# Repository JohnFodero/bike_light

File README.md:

# bike_light
A lithium powered, uC controlled bike light. For safety!

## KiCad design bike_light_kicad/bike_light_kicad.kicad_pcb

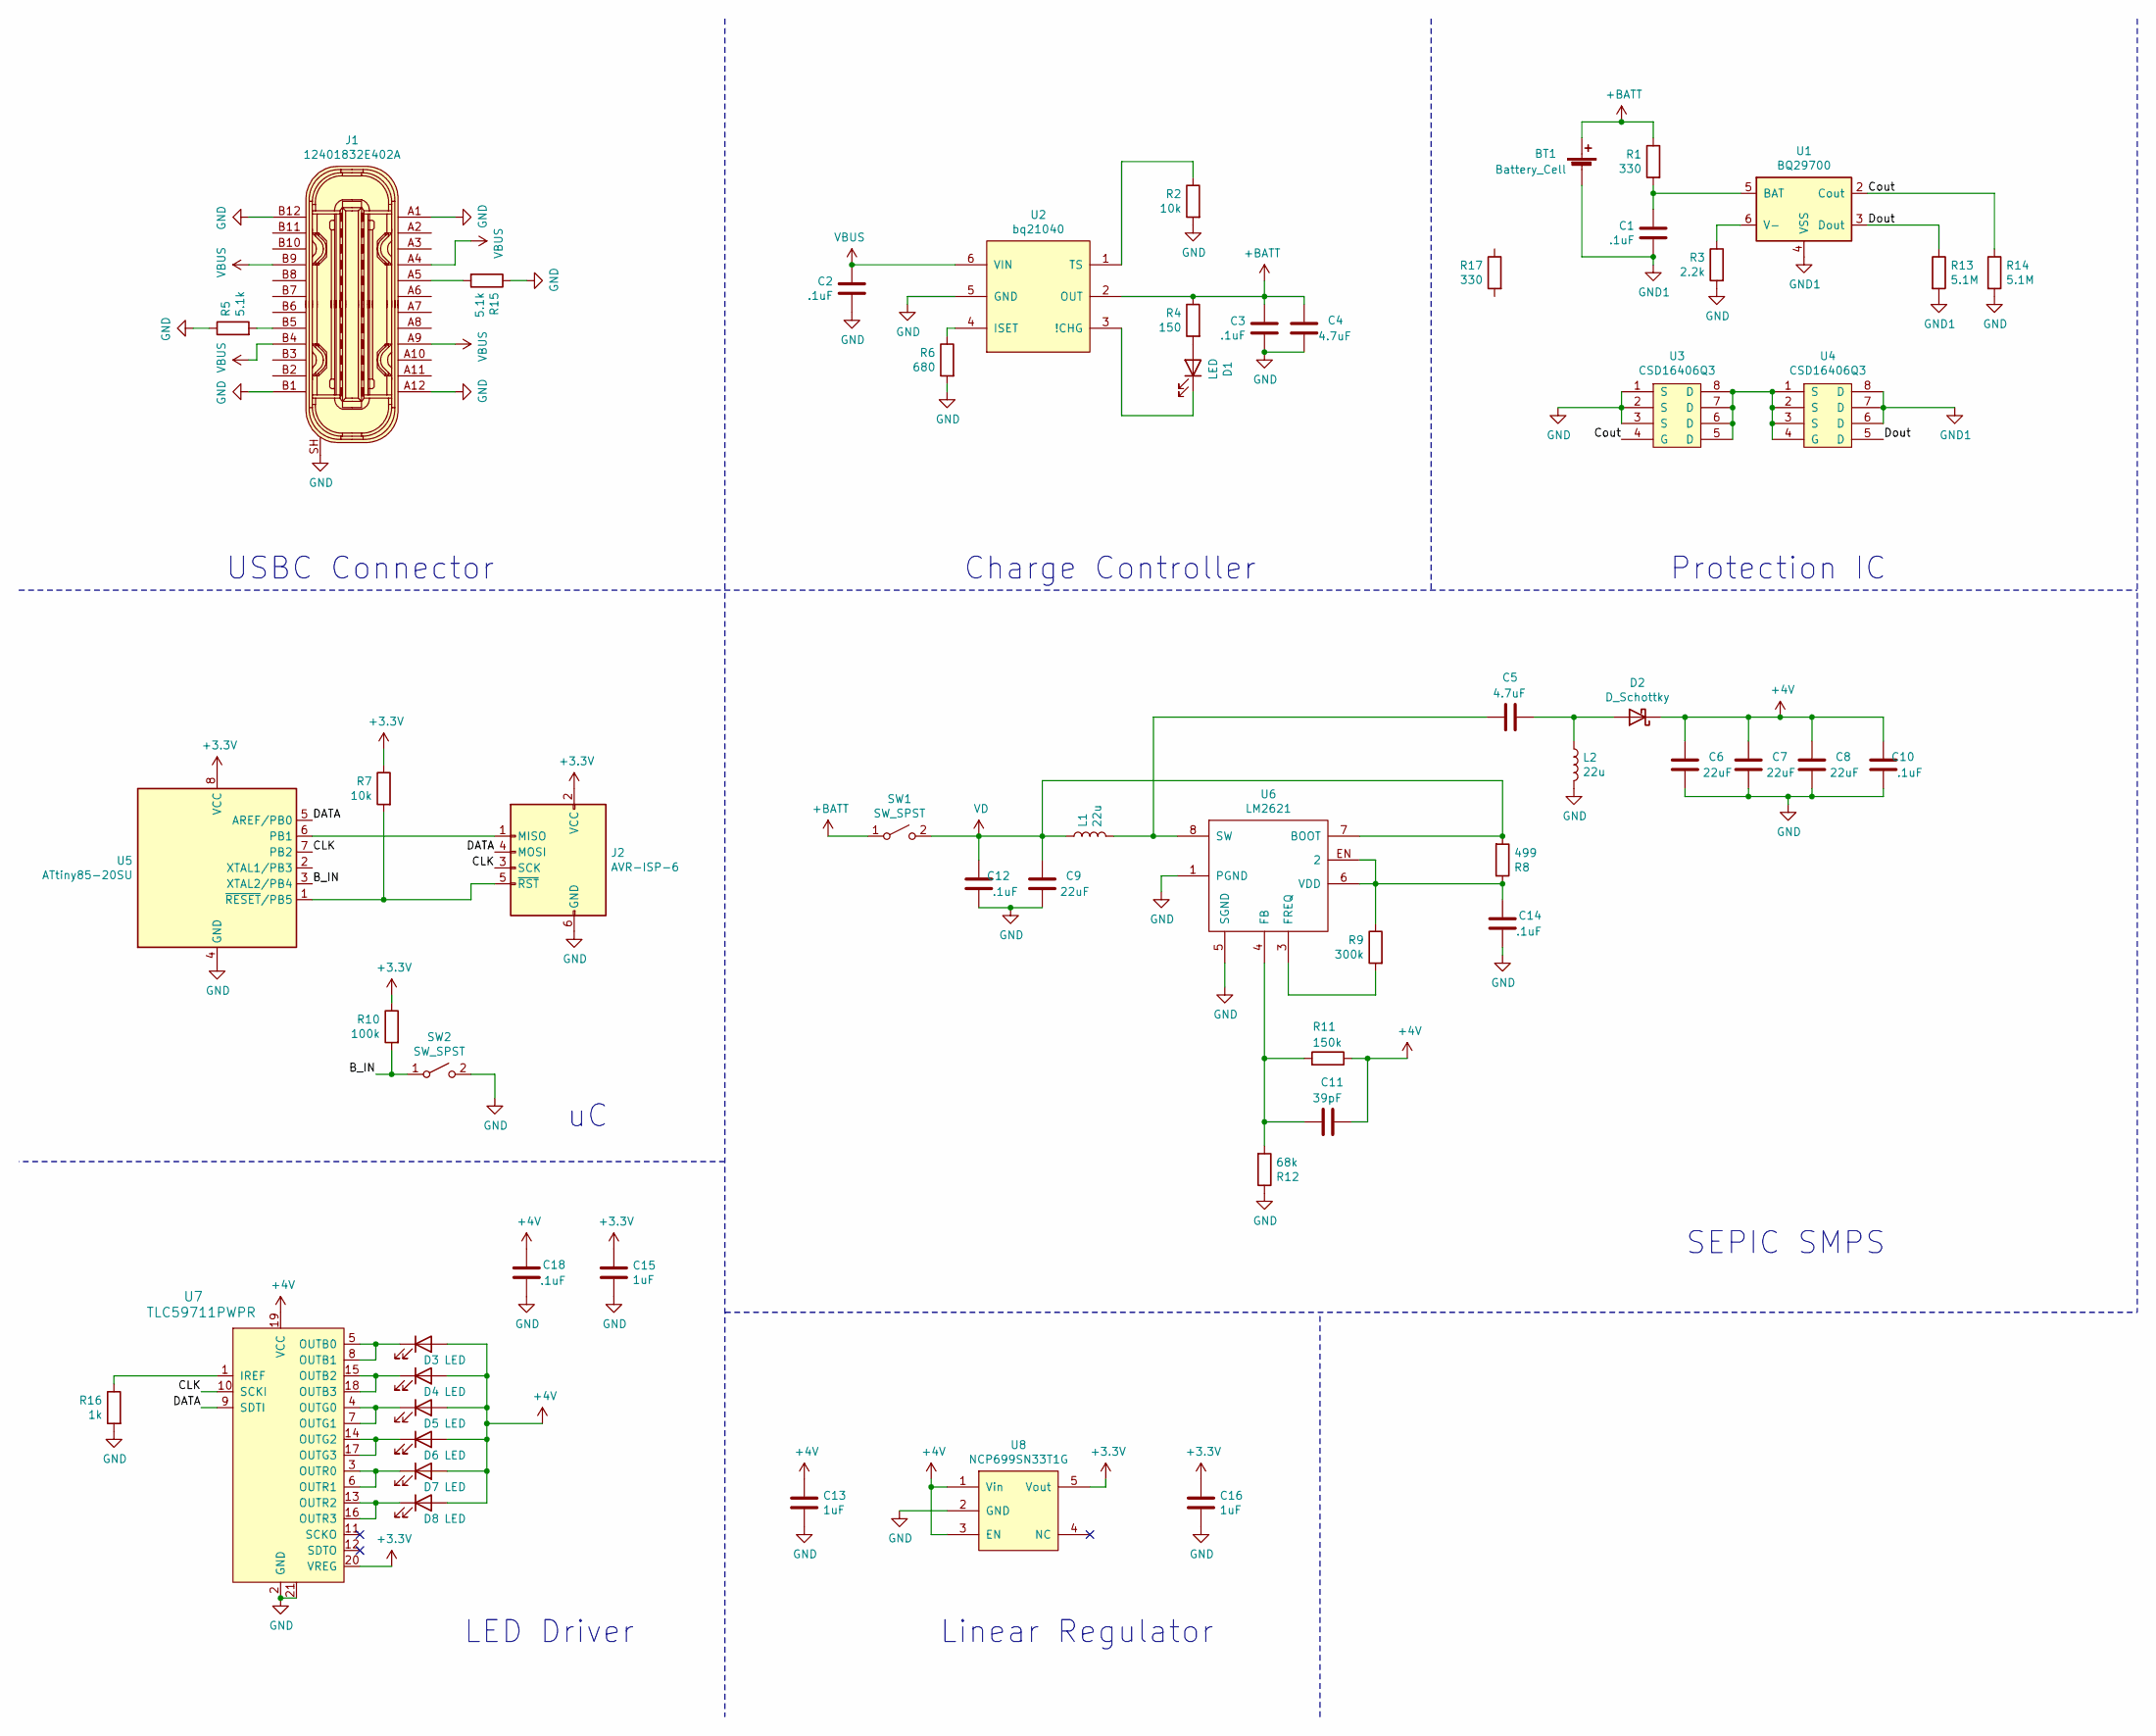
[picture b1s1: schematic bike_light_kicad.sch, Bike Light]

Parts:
BT1: Battery_Cell; 36-254-ND; MPN PRT-12895; Digi-Key_PN 1568-1488-ND
C1, C2, C3, C10, C12, C14, C18: .1uF; C_0603; MPN C0603C104M4RACTU; Digi-Key_PN 399-1099-1-ND
C4: 4.7uF; C_0603; MPN CL10A475MO8NNNC; Digi-Key_PN 1276-1904-1-ND
C5: 4.7uF; C_1206; MPN C1206C475K4RACTU; Digi-Key_PN 399-3524-1-ND
C6, C7, C8, C9: 22uF; C_0805; MPN GRM21BC81C226ME44L; Digi-Key_PN 490-9956-1-ND
C11: 39pF; C_0603; MPN C0603C390J5GACTU; Digi-Key_PN 399-7911-1-ND
C13, C15, C16: 1uF; C_0603; MPN C0603C105M4RACTU; Digi-Key_PN 399-11136-1-ND
D1: LED; LED_0603; MPN LTST-C190KFKT; Digi-Key_PN 160-1434-1-ND
D2: D_Schottky; D_SOD-323F; MPN PMEG2015EJ,115; Digi-Key_PN 1727-3861-2-ND
D3, D4, D5, D6, D7, D8: LED; 1510-2183-1-ND; MPN SPMWHT541ML5XATMS6; Digi-Key_PN 1510-2183-1-ND
J1: 12401832E402A; USB_Type_C_Female__12401610E4_2A; MPN 12401832E402A; Digi-Key_PN 12401832E402ACT-ND
J2: AVR-ISP-6; PINHEAD1-6; MPN 4173; Digi-Key_PN 1528-2946-ND
L1, L2: 22u; SRU1038-220YCT-ND; MPN SRU1038-220Y; Digi-Key_PN SRU1038-220YCT-ND
R1, R17: 330; R_0603; MPN RC0603FR-07330RL; Digi-Key_PN 311-330HRCT-ND
R2, R7: 10k; R_0603; MPN RC0603FR-0710KL; Digi-Key_PN 311-10.0KHRCT-ND
R3: 2.2k; R_0603; MPN RC0603FR-072K2L; Digi-Key_PN 311-2.20KHRCT-ND
R4: 150; R_0603; MPN RC0603FR-07150RL; Digi-Key_PN 311-150HRCT-ND
R5, R15: 5.1k; R_0603; MPN RC0603FR-075K1L; Digi-Key_PN 311-5.10KHRCT-ND
R6: 680; R_0603; MPN RT0603FRE07680RL; Digi-Key_PN YAG3356CT-ND
R8: 499; R_0603; MPN RC0603FR-07499RL; Digi-Key_PN 311-499HRCT-ND
R9: 300k; R_0603; MPN RC0603FR-07300KL; Digi-Key_PN 311-300KHRCT-ND
R10: 100k; R_0603; MPN RC0603FR-07100KL; Digi-Key_PN 311-100KHRCT-ND
R11: 150k; R_0603; MPN RC0603FR-07150KL; Digi-Key_PN 311-150KHRCT-ND
R12: 68k; R_0603; MPN RC0603FR-0768KL; Digi-Key_PN 311-68.0KHRCT-ND
R13, R14: 5.1M; R_0603; MPN RC0603JR-075M1L; Digi-Key_PN 311-5.1MGRCT-ND
R16: 1k; R_0603; MPN RC0603FR-071KL; Digi-Key_PN 311-1.00KHRCT-ND
SW1: SW_SPST; CKC5106-ND; MPN L101011MS02Q; Digi-Key_PN CKC5106-ND
SW2: SW_SPST
U1: BQ29700; WSON6_1.5x1.5mm_Pitch0.5mm; MPN BQ29700DSER; Digi-Key_PN 296-43985-1-ND
U2: bq21040; SOT-23-6; MPN BQ21040DBVR; Digi-Key_PN 296-47315-1-ND
U3, U4: CSD16406Q3; TDFN-8-1EP; MPN CSD16406Q3; Digi-Key_PN 296-24251-1-ND
U5: ATtiny85-20SU; SOIJ-8_5.3x5.3mm_Pitch1.27mm; MPN ATTINY85-20SUR; Digi-Key_PN ATTINY85-20SURCT-ND
U6: LM2621; VSSOP-8_3.0x3.0mm_Pitch0.65mm; MPN LM2621MMX/NOPB; Digi-Key_PN LM2621MMX/NOPBCT-ND
U7: TLC59711PWPR; TSSOP-20-1EP_W4.4mm; MPN TLC59711PWPR; Digi-Key_PN 296-36745-1-ND
U8: NCP699SN33T1G; SOT-23-5; MPN NCP699SN33T1G; Digi-Key_PN NCP699SN33T1GOSCT-ND

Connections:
+3V3: C15.1, C16.1, J2.2 (VCC), R7.1, R10.1, U5.8 (VCC), U7.20 (VREG), U8.5 (Vout)
+4V: C6.1, C7.1, C8.1, C10.1, C11.1, C13.1, C18.1, D2.1 (K), D3.2 (A), D4.2 (A), D5.2 (A), D6.2 (A), D7.2 (A), D8.2 (A), R11.1, U7.19 (VCC), U8.1 (Vin), U8.3 (EN)
+BATT: BT1.1 (+), C3.1, C4.1, R1.1, R4.1, SW1.1 (A), U2.2 (OUT)
/B_IN: R10.2, SW2.1 (A), U5.3 (XTAL2/PB4)
/CLK: J2.3 (SCK), U5.7 (PB2), U7.10 (SCKI)
/Cout: R14.1, U1.2 (Cout), U3.4 (G)
/DATA: J2.4 (MOSI), U5.5 (AREF/PB0), U7.9 (SDTI)
/Dout: R13.1, U1.3 (Dout), U4.5 (D)
GND: C2.2, C3.2, C4.2, C6.2, C7.2, C8.2, C9.2, C10.2, C12.2, C13.2, C14.2, C15.2, C16.2, C18.2, J1.A1, J1.A12, J1.B1, J1.B12, J1.SH, J2.6 (GND), L2.2, R2.2, R3.2, R5.1, R6.2, R12.1, R14.2, R15.1, R16.2, SW2.2 (B), U2.5 (GND), U3.1 (S), U3.2 (S), U3.3 (S), U5.4 (GND), U6.1 (PGND), U6.5 (SGND), U7.2 (GND), U7.21, U8.2 (GND)
GND1: BT1.2 (-), C1.2, R13.2, U1.4 (VSS), U4.6 (D), U4.7 (D), U4.8 (D)
unnamed: C1.1, R1.2, U1.5 (BAT)
unnamed: C5.1, L1.2, U6.8 (SW)
unnamed: C5.2, D2.2 (A), L2.1
unnamed: C11.2, R11.2, R12.2, U6.4 (FB)
unnamed: C14.1, R8.1, R9.1, U6.6 (VDD), U6.EN (2)
unnamed: D1.1 (K), U2.3 (!CHG)
unnamed: D1.2 (A), R4.2
unnamed: D3.1 (K), U7.5 (OUTB0), U7.8 (OUTB1)
unnamed: D4.1 (K), U7.15 (OUTB2), U7.18 (OUTB3)
unnamed: D5.1 (K), U7.4 (OUTG0), U7.7 (OUTG1)
unnamed: D6.1 (K), U7.14 (OUTG2), U7.17 (OUTG3)
unnamed: D7.1 (K), U7.3 (OUTR0), U7.6 (OUTR1)
unnamed: D8.1 (K), U7.13 (OUTR2), U7.16 (OUTR3)
unnamed: J1.A5, R15.2
unnamed: J1.B5, R5.2
unnamed: J2.1 (MISO), U5.6 (PB1)
unnamed: J2.5 (~RST), R7.2, U5.1 (~RESET~/PB5)
unnamed: R2.1, U2.1 (TS)
unnamed: R3.1, U1.6 (V-)
unnamed: R6.1, U2.4 (ISET)
unnamed: R9.2, U6.3 (FREQ)
unnamed: R16.1, U7.1 (IREF)
unnamed: U3.5 (D), U3.6 (D), U3.7 (D), U3.8 (D), U4.1 (S), U4.2 (S), U4.3 (S), U4.4 (G)
VBUS: C2.1, J1.A4, J1.A9, J1.B4, J1.B9, U2.6 (VIN)
VD: C9.1, C12.1, L1.1, R8.2, SW1.2 (B), U6.7 (BOOT)

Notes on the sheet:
USBC Connector
Charge Controller
Protection IC
SEPIC SMPS
LED Driver
Linear Regulator

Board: 2 copper layers, 56 parts (0 on the bottom side), 35 nets, no tracks yet.

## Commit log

2020-08-25 kicad bare bones project
2020-08-27 added basic SEPIC topology, and PWM controller to schem
2020-08-27 Adding library for symbols/footprints we manually create
2020-08-30 Schematic organization, SPMS PNs, Charge controller IC symbol, USBC connections
2020-09-01 component defs
2020-09-01 added cahche lib
2020-09-03 Linear reg added, ground error fixed, LED connections, button input, power switch
2020-09-03 charge controller current resistor, ground correction
2020-09-03 Added simulation of basic open loop SEPIC to verify design equations, especially under 2.8A switch peak current of IC
2020-09-04 added some specific part numbers
2020-09-07 Johns schematic updates
2020-09-07 added components in standard formatt to smps stage
2020-09-08 added platformio project
2020-09-16 Footprints added, new manual lib
2020-09-16 Added components to .kicad_pcb file
